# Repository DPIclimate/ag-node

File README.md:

<h2 align="center">
    Agriculture Node
</h2>
<p align="center">
  <a href="#about">About</a> •
  <a href="#schematic">Schematic</a> •
  <a href="#protocol / algorithm">Protocol</a> •
  <a href="#firmware docs">Docs</a> •
  <a href="#license">License</a>
</p>

<p align="center">
  
</p>

## About

The agriculture node (ag-node) is an automatic multi-weigh-station for measuring the live-weight of sheep  in remote locations. The station can be situated against a trough for which sheep weights will be recorded as they access feed or water. An in-built LoRaWAN radio sends data (containing live-weight information) back to a local gateway and onto the end user. Additional interfaces are provided, including; SDI-12, I<sub>2</sub>C and OneWire to allow for various sensors to be connected to the device (such as trough level sensors, temperature monitors etc.).

## Schematic

The devices schematic can be found at: [schematic.pdf](https://github.com/DPIclimate/ag-node/blob/master/figures/schematic.pdf)

Basic components are summarised in the below image. Where A is the analog-to-digital converter, B is the LoRaWAN communication infrastructure and C is the peripheral sensor connectors (I<sub>2</sub>C, OneWire and SDI-12).

<div align="middle"> 
	
</div>

## Protocol / Algorithm

As the device operates autonomously (sheep are weighed in an unsupervised manner) an algorithm to capture the maximum stable weight (and an error representation) is provided.

The protocol is explained below and a visual representation is provided.

1. A weight is captured (triggered by a sheep stepping on a scale) consisting of a time-series of weights while the sheep is on the platform

2. This time-series data is sliced into groups of 5 values

3. The slope between the first and last value is calculated (where values < 0.1) are discarded as they represent unstable weights

4. The Root Mean Square Error (RMSE) of the fitted line is calculated

5. The average of the 5 points are taken

6. An evaluation of the new weight is made against previous slices (see figure below under the Method `Evaluate` for an equation that represents this)

<div align="middle"> 
	
</div>

## Firmware Docs

Firmware documentation can be found [here](https://dpiclimate.github.io/ag-node)

An illustration of the devices operations can be found below:

<div align="middle"> 
	
</div>

## License

Ag-node is MIT licensed, as found in the [LICENSE](https://github.com/DPIclimate/ag-node/blob/master/LICENSE) file.

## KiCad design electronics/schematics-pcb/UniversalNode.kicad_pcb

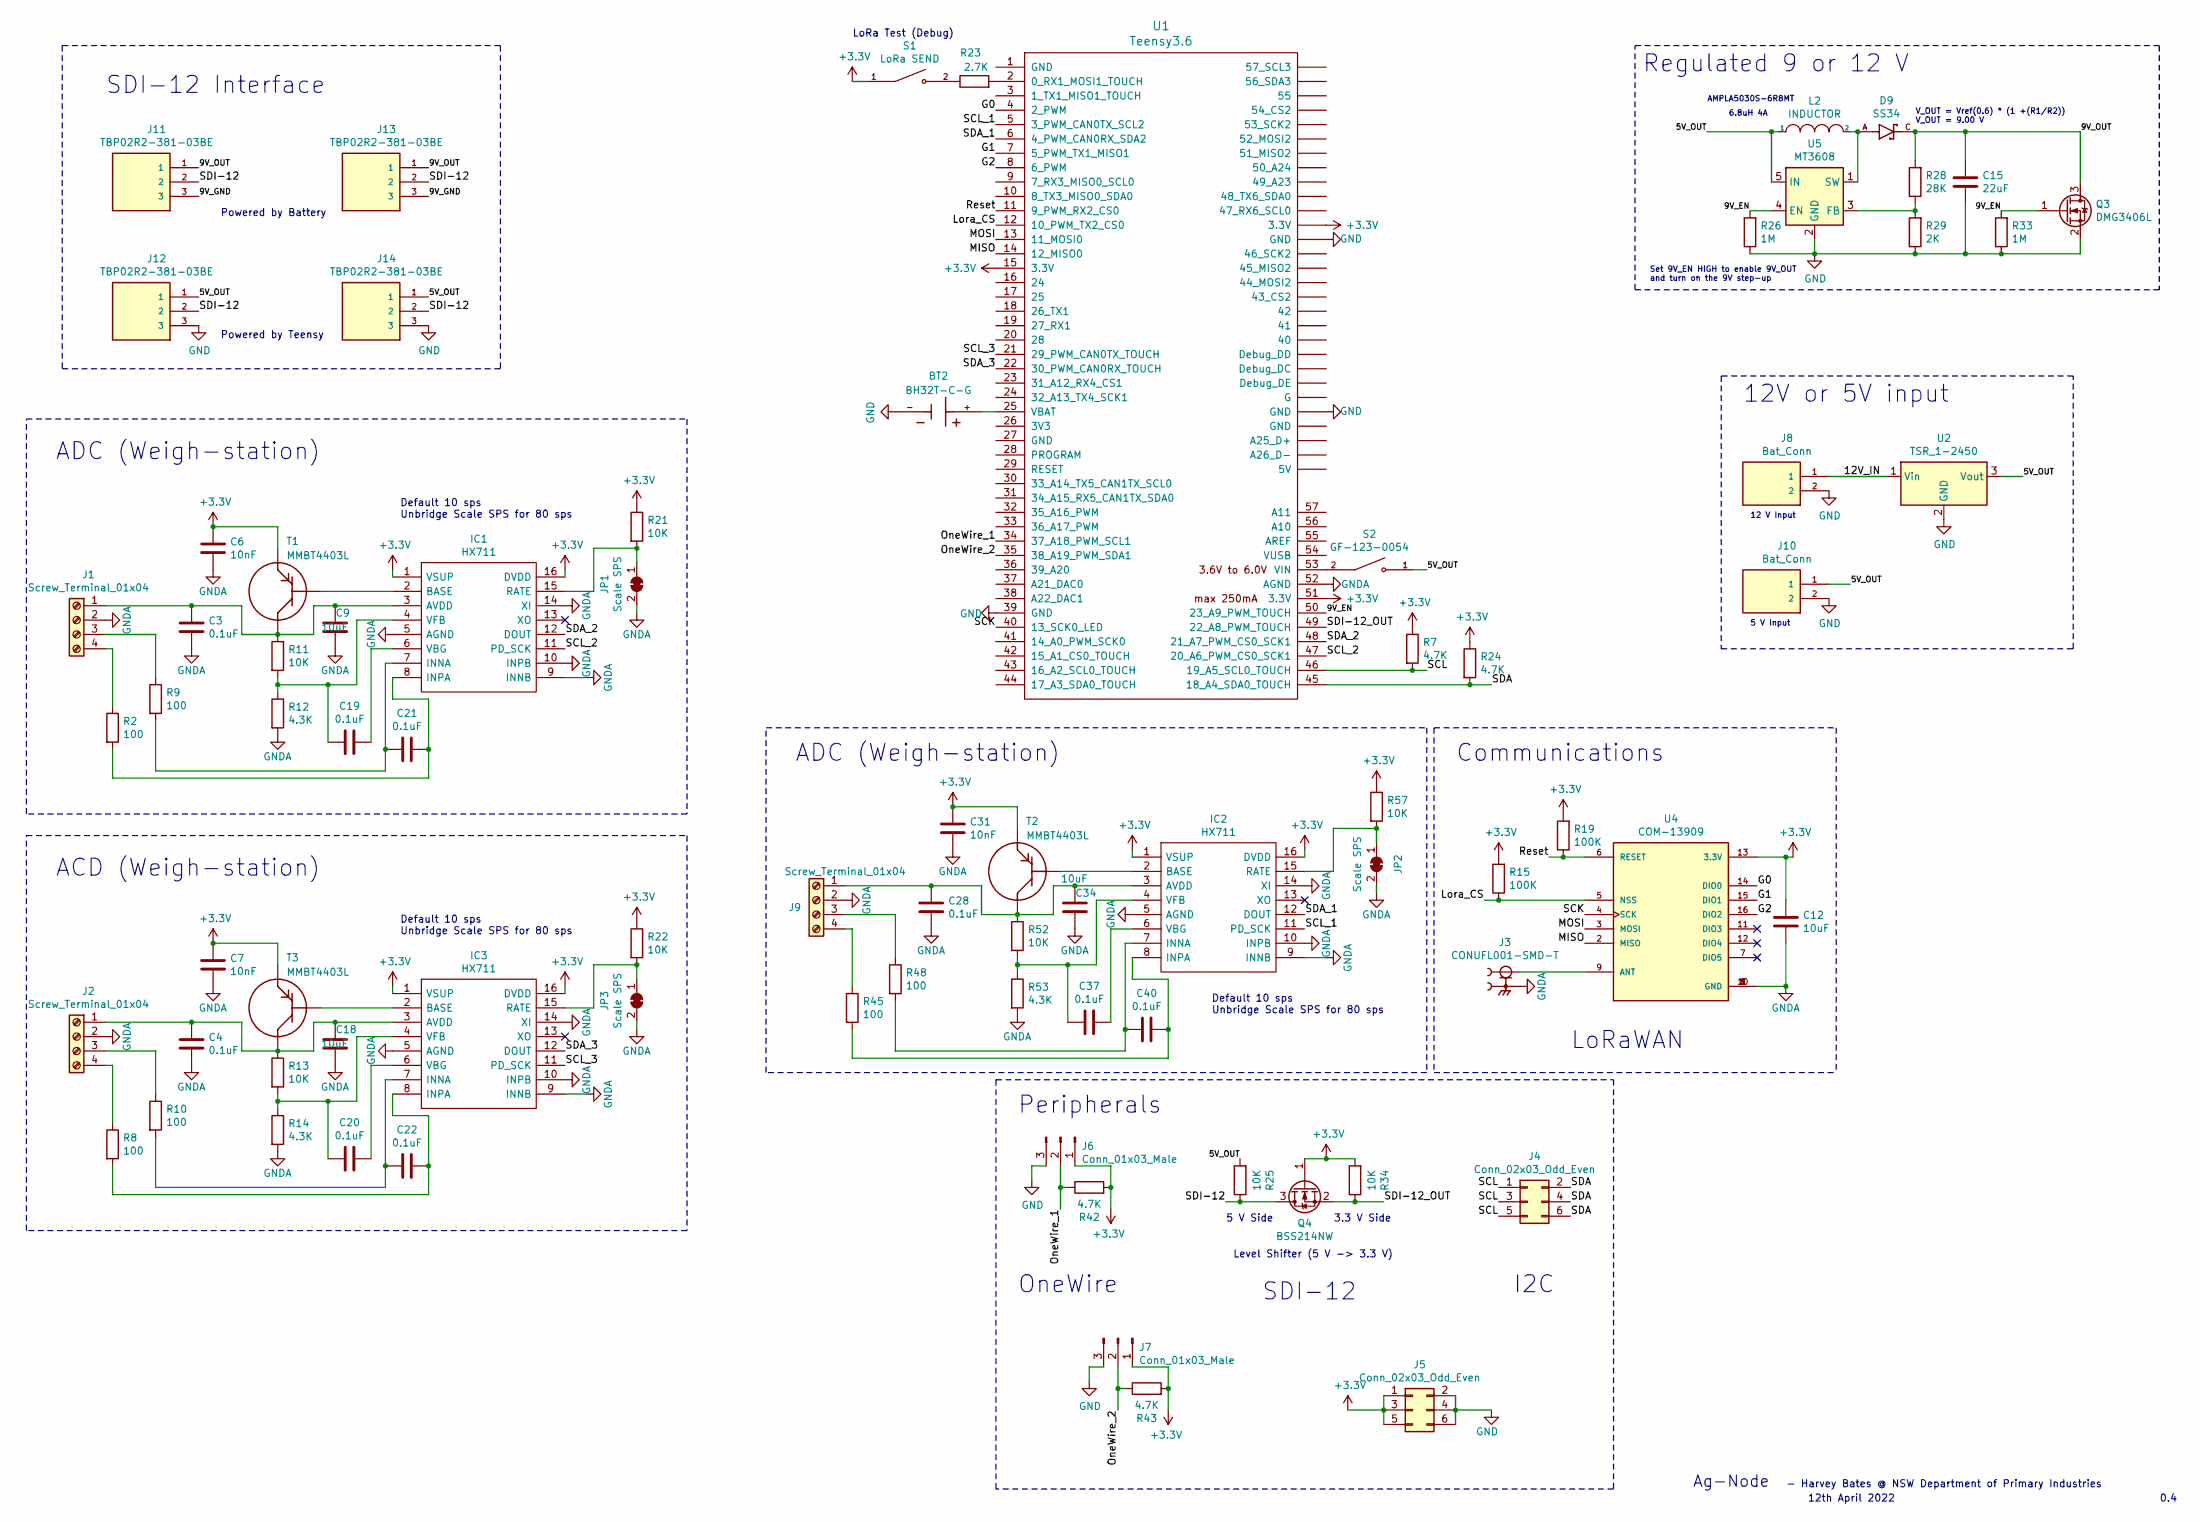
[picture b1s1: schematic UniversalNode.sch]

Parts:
BT2: BH32T-C-G; BAT_BH32T-C-G; PARTREV B
C3, C4, C19, C20, C21, C22, C28, C37, C40: 0.1uF; C_0805_2012Metric
C6, C7, C31: 10nF; C_0805_2012Metric
C9, C12, C18, C34: 10uF; CP_Elec_5x5.4
C15: 22uF; CP_Elec_6.3x5.9
D9: SS34; DIOM7959X265N; PARTREV 31 Aug 2016
IC1, IC2, IC3: HX711; SOIC127P600X160-16N; Manufacturer_Part_Number HX711
J1, J2, J9: Screw_Terminal_01x04; OSTOQ043250
J3: CONUFL001-SMD-T; LINX_CONUFL001-SMD-T; PARTREV B
J4, J5: Conn_02x03_Odd_Even; PinSocket_2x03_P2.54mm_Vertical
J6, J7: Conn_01x03_Male; PinSocket_1x03_P2.54mm_Vertical
J8, J10: Bat_Conn; 102-6492-ND‎
J11, J12, J13, J14: TBP02R2-381-03BE; CUI_TBP02R2-381-03BE
JP1, JP2, JP3: Scale SPS; SolderJumper-2_P1.3mm_Bridged_Pad1.0x1.5mm
L2: INDUCTOR; AMPLA5030S-6R8MT
Q3: DMG3406L; SOT-23
Q4: BSS214NW; SOT-323_SC-70
R2, R8, R9, R10, R45, R48: 100; R_0805_2012Metric
R7, R24, R42, R43: 4.7K; R_0805_2012Metric
R11, R13, R21, R22, R25, R34, R52, R57: 10K; R_0805_2012Metric
R12, R14, R53: 4.3K; R_0805_2012Metric
R15, R19: 100K; R_0805_2012Metric
R23: 2.7K; R_0805_2012Metric
R26, R33: 1M; R_0805_2012Metric
R28: 28K; R_0805_2012Metric
R29: 2K; R_0805_2012Metric
S1: LoRa SEND; SW_PTS636_SM43J_SMTR_LFS; PARTREV 27 mar 19
S2: GF-123-0054; SW_GF-123-0054; PARTREV May 20, 2003
T1, T2, T3: MMBT4403L; SOT23
U1: Teensy3.6; Teensy35_36
U2: TSR_1-2450; Converter_DCDC_TRACO_TSR-1_THT
U4: COM-13909; MOD_COM-13909
U5: MT3608; SOT-23-6

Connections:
+3V3: C6.1, C7.1, C12.1, C31.1, IC1.1 (VSUP), IC1.16 (DVDD), IC2.1 (VSUP), IC2.16 (DVDD), IC3.1 (VSUP), IC3.16 (DVDD), J5.1, J5.3, J5.5, J6.1, J7.1, Q4.1 (G), R7.1, R15.2, R19.2, R21.1, R22.1, R24.1, R34.2, R42.2, R43.2, R57.1, S1.1, T1.2, T2.2, T3.2, U1.15 (3.3V), U1.51 (3.3V), U1.~ (3.3V), U4.13 (3.3V)
/5V_OUT: J10.1, J12.1, J14.1, L2.1, R25.2, S2.1, U2.3 (Vout), U5.5 (IN)
/9V_EN: Q3.1 (G), R26.2, R33.2, U1.50 (23_A9_PWM_TOUCH), U5.4 (EN)
/9V_GND: J11.3, J13.3
/9V_OUT: C15.1, D9.C, J11.1, J13.1, Q3.3 (D), R28.2
/12V_IN: J8.1, U2.1 (Vin)
/G0: U1.4 (2_PWM), U4.14 (DIO0)
/G1: U1.7 (5_PWM_TX1_MISO1), U4.15 (DIO1)
/G2: U1.8 (6_PWM), U4.16 (DIO2)
/Lora_CS: R15.1, U1.12 (10_PWM_TX2_CS0), U4.5 (NSS)
/MISO: U1.14 (12_MISO0), U4.2 (MISO)
/MOSI: U1.13 (11_MOSI0), U4.3 (MOSI)
/OneWire_1: J6.2, R42.1, U1.34 (37_A18_PWM_SCL1)
/OneWire_2: J7.2, R43.1, U1.35 (38_A19_PWM_SDA1)
/Reset: R19.1, U1.11 (9_PWM_RX2_CS0), U4.6 (RESET)
/SCK: U1.40 (13_SCK0_LED), U4.4 (SCK)
/SCL: J4.1, J4.3, J4.5, R7.2, U1.46 (19_A5_SCL0_TOUCH)
/SCL_1: IC2.11 (PD_SCK), U1.5 (3_PWM_CAN0TX_SCL2)
/SCL_2: IC1.11 (PD_SCK), U1.47 (20_A6_PWM_CS0_SCK1)
/SCL_3: IC3.11 (PD_SCK), U1.21 (29_PWM_CAN0TX_TOUCH)
/SDA: J4.2, J4.4, J4.6, R24.2, U1.45 (18_A4_SDA0_TOUCH)
/SDA_1: IC2.12 (DOUT), U1.6 (4_PWM_CAN0RX_SDA2)
/SDA_2: IC1.12 (DOUT), U1.48 (21_A7_PWM_CS0_SCK1)
/SDA_3: IC3.12 (DOUT), U1.22 (30_PWM_CAN0RX_TOUCH)
/SDI-12: J11.2, J12.2, J13.2, J14.2, Q4.3 (D), R25.1
/SDI-12_OUT: Q4.2 (S), R34.1, U1.49 (22_A8_PWM_TOUCH)
GND: BT2.-, C15.2, J5.2, J5.4, J5.6, J6.3, J7.3, J8.2, J10.2, J12.3, J14.3, Q3.2 (S), R26.1, R29.1, R33.1, U1.39 (GND), U1.~ (3.3V), U2.2 (GND), U5.2 (GND)
GNDA: C3.2, C4.2, C6.2, C7.2, C9.2, C12.2, C18.2, C28.2, C31.2, C34.2, IC1.5 (AGND), IC1.9 (INNB), IC1.10 (INPB), IC1.14 (XI), IC2.5 (AGND), IC2.9 (INNB), IC2.10 (INPB), IC2.14 (XI), IC3.5 (AGND), IC3.9 (INNB), IC3.10 (INPB), IC3.14 (XI), J1.2, J2.2, J3.2, J3.3, J9.2, JP1.2 (B), JP2.2 (B), JP3.2 (B), R12.2, R14.2, R53.2, U1.52 (AGND), U4.1 (GND), U4.8 (GND), U4.10 (GND)
unnamed: BT2.+, U1.25 (VBAT)
unnamed: C3.1, C9.1, IC1.3 (AVDD), J1.1, R11.1, T1.3
unnamed: C4.1, C18.1, IC3.3 (AVDD), J2.1, R13.1, T3.3
unnamed: C19.1, IC1.6 (VBG)
unnamed: C19.2, IC1.4 (VFB), R11.2, R12.1
unnamed: C20.1, IC3.6 (VBG)
unnamed: C20.2, IC3.4 (VFB), R13.2, R14.1
unnamed: C21.1, IC1.7 (INNA), R9.2
unnamed: C21.2, IC1.8 (INPA), R2.2
unnamed: C22.1, IC3.7 (INNA), R10.2
unnamed: C22.2, IC3.8 (INPA), R8.2
unnamed: C28.1, C34.1, IC2.3 (AVDD), J9.1, R52.1, T2.3
unnamed: C37.1, IC2.6 (VBG)
unnamed: C37.2, IC2.4 (VFB), R52.2, R53.1
unnamed: C40.1, IC2.7 (INNA), R48.2
unnamed: C40.2, IC2.8 (INPA), R45.2
unnamed: D9.A, L2.2, U5.1 (SW)
unnamed: IC1.2 (BASE), T1.1
unnamed: IC1.15 (RATE), JP1.1 (A), R21.2
unnamed: IC2.2 (BASE), T2.1
unnamed: IC2.15 (RATE), JP2.1 (A), R57.2
unnamed: IC3.2 (BASE), T3.1
unnamed: IC3.15 (RATE), JP3.1 (A), R22.2
unnamed: J1.3, R9.1
unnamed: J1.4, R2.1
unnamed: J2.3, R10.1
unnamed: J2.4, R8.1
unnamed: J3.1, U4.9 (ANT)
unnamed: J9.3, R48.1
unnamed: J9.4, R45.1
unnamed: R23.1, S1.2
unnamed: R23.2, U1.2 (0_RX1_MOSI1_TOUCH)
unnamed: R28.1, R29.2, U5.3 (FB)
unnamed: S2.2, U1.53 (VIN)

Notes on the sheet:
Ag-Node
12th April 2022
- Harvey Bates @ NSW Department of Primary Industries
0.4
Powered by Battery
Powered by Teensy
SDI-12 Interface
ACD (Weigh-station)
Default 10 sps Unbridge Scale SPS for 80 sps
ADC (Weigh-station)
5 V Input
12V or 5V input
12 V Input
Set 9V_EN HIGH to enable 9V_OUT and turn on the 9V step-up
Regulated 9 or 12 V
V_OUT = Vref(0.6) * (1 +(R1/R2)) V_OUT = 9.00 V
AMPLA5030S-6R8MT
6.8uH 4A
LoRa Test (Debug)
OneWire
I2C
SDI-12
Level Shifter (5 V -> 3.3 V)
5 V Side
3.3 V Side
Peripherals
LoRaWAN
Communications

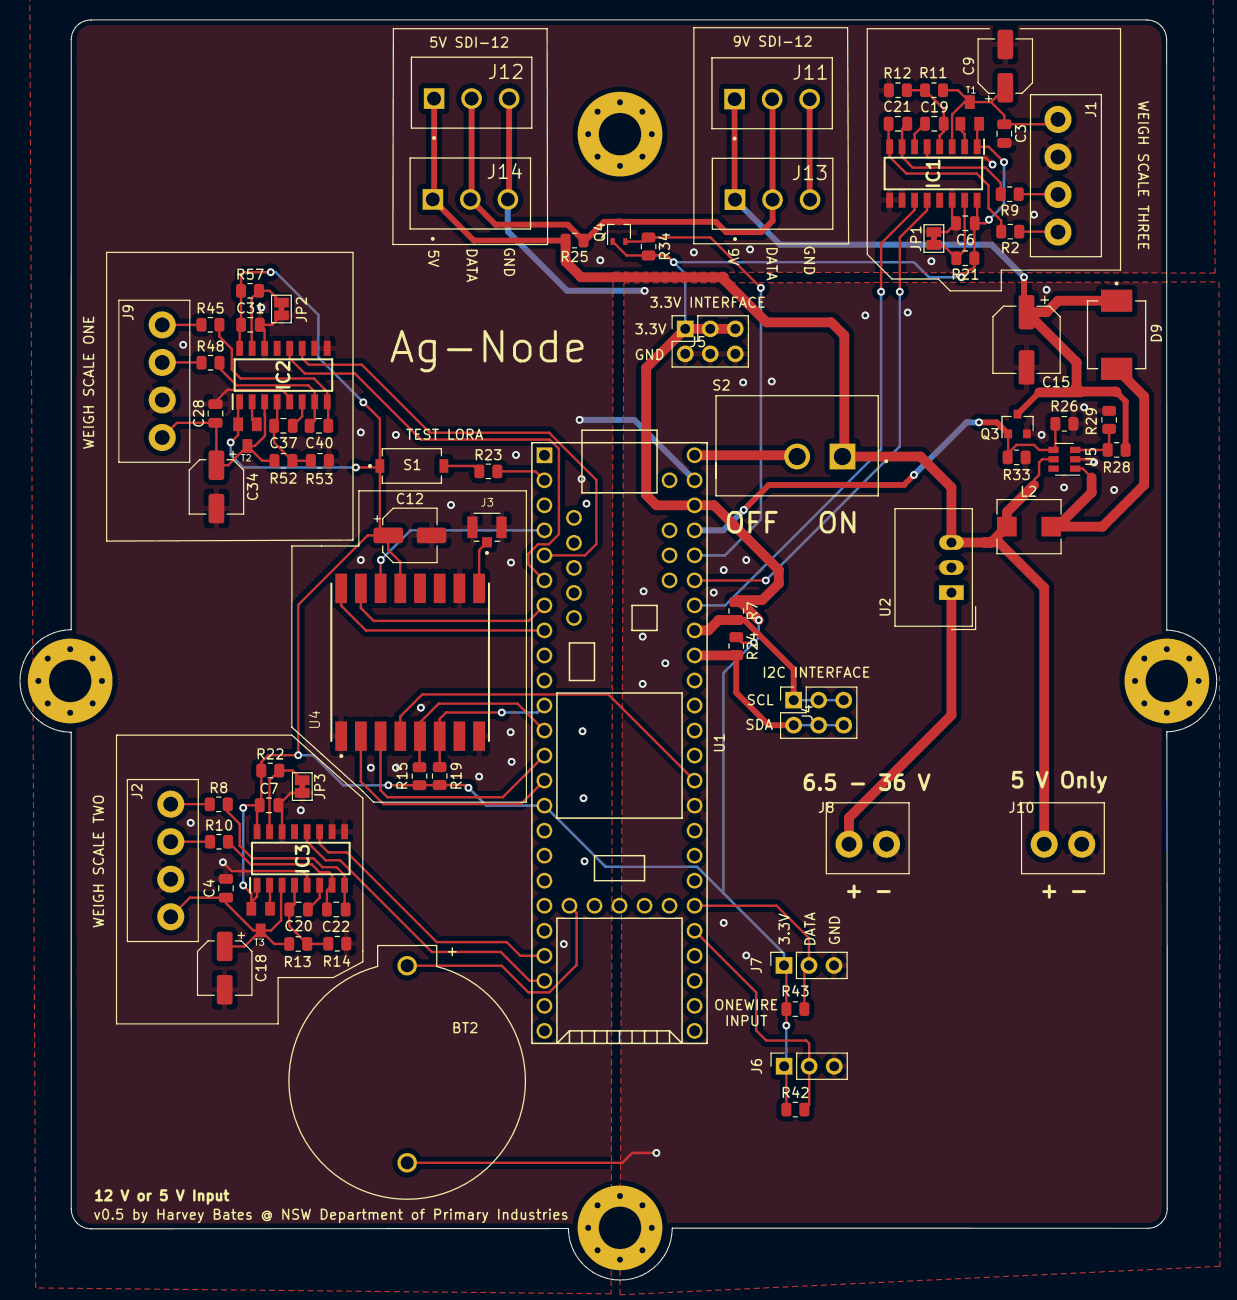
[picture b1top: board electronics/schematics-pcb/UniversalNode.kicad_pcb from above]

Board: 2 copper layers, 121.5 x 127.9 mm, 79 parts (0 on the bottom side), 62 nets.

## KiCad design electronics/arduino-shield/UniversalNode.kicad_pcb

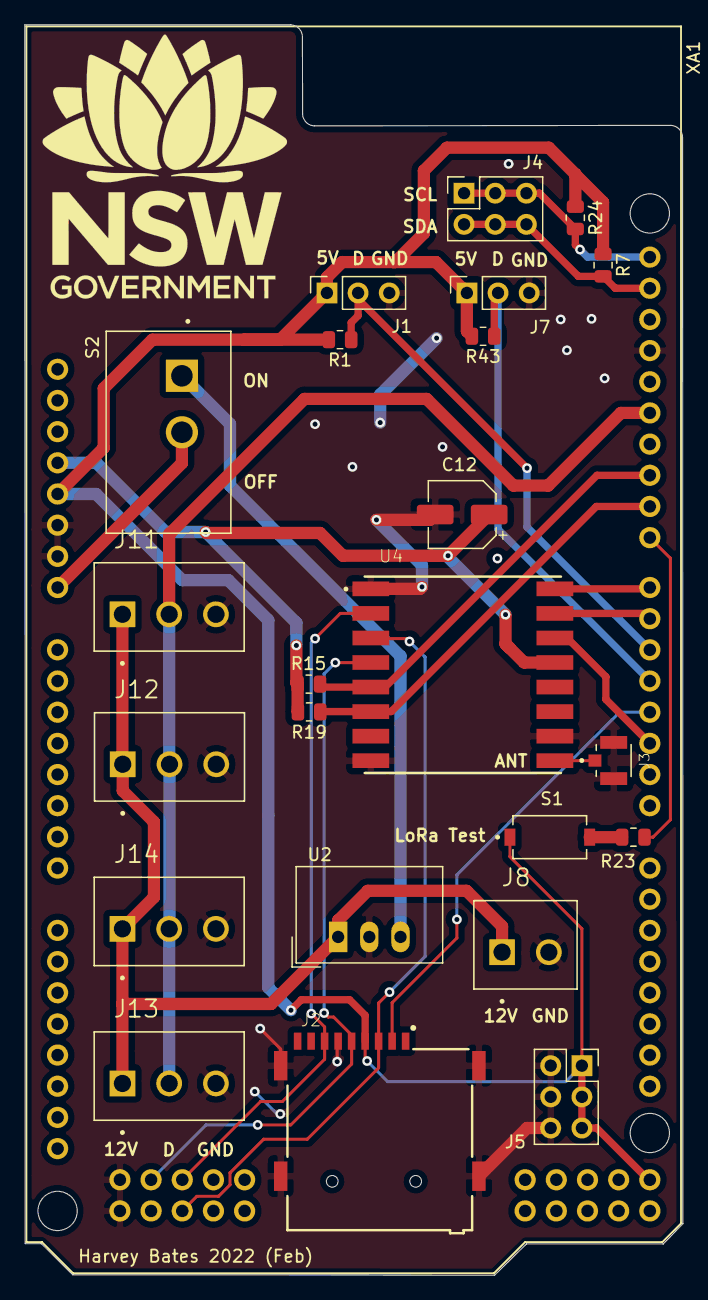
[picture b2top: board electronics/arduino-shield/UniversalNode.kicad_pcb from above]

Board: 2 copper layers, 53.6 x 101.9 mm, 24 parts (0 on the bottom side), 23 nets.

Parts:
C12: 10uF; CP_Elec_5x5.4
J1, J7: Conn_01x03_Male; PinSocket_1x03_P2.54mm_Vertical
J2: MEM2075-00-140-01-A; GCT_MEM2075-00-140-01-A
J3: CONUFL001-SMD-T; LINX_CONUFL001-SMD-T
J4, J5: Conn_02x03_Odd_Even; PinSocket_2x03_P2.54mm_Vertical
J8: Bat_Conn; CUI_TBP02R2-381-02BE
J11, J12, J13, J14: TBP02R2-381-03BE; CUI_TBP02R2-381-03BE
R1, R7, R24, R43: 4.7K; R_0805_2012Metric
R15, R19: 100K; R_0805_2012Metric
R23: 2.7K; R_0805_2012Metric
S1: LoRa SEND; SW_PTS636_SM43J_SMTR_LFS
S2: GF-123-0054; SW_GF-123-0054
U2: TSR_1-2450; Converter_DCDC_TRACO_TSR-1_THT
U4: COM-13909; MOD_COM-13909
XA1: Arduino_Mega2560_Shield

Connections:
+3V3: C12.1, R15.2, R19.2, U4.13, XA1.3V3
/5V: J1.1, J2.P4, J5.1, J5.3, J5.5, J7.1, R1.2, R7.1, R24.1, R43.2, S1.1, XA1.5V1, XA1.5V3
/5V_OUT: S2.1, U2.3
/12V_IN: J8.1, J11.1, J12.1, J13.1, J14.1, U2.1
/G0: U4.14, XA1.D2
/G1: U4.15, XA1.D6
/G2: U4.16, XA1.D7
/Lora_CS: R15.1, U4.5, XA1.D10
/MISO: J2.P7, U4.2, XA1.D50
/MOSI: J2.P3, U4.3, XA1.D51
/OneWire_1: J7.2, R43.1, XA1.D4
/OneWire_2: J1.2, R1.1, XA1.D5
/Reset: R19.1, U4.6, XA1.D9
/SCK: J2.P5, U4.4, XA1.D52
/SCL: J4.1, J4.3, J4.5, R24.2, XA1.SCL
/SDA: J4.2, J4.4, J4.6, R7.2, XA1.SDA
/SDI-12: J11.2, J12.2, J13.2, J14.2, XA1.D12
/SD_CS: J2.P2, XA1.D3
GND: C12.2, J1.3, J2.P6, J2.SH1, J2.SH2, J2.SH3, J2.SH4, J3.2, J3.3, J5.2, J5.4, J5.6, J7.3, J8.2, J11.3, J12.3, J13.3, J14.3, U2.2, U4.1, U4.8, U4.10, XA1.GND1, XA1.GND2, XA1.GND3, XA1.GND5, XA1.GND6
unnamed: J3.1, U4.9
unnamed: R23.1, S1.2
unnamed: R23.2, XA1.D8
unnamed: S2.2, XA1.VIN

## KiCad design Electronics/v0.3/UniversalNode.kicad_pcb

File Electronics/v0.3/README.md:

## Version 0.3
- Uses Teensy 3.6 as mainboard controller (run at a low clock speed) and defaults to sleep
- Has 3 weigh station ports (controlled by a HX711 and a ATMega328) 
- ATMega328's have interrupts connected to the teensy to wake it up when they want to transfer some data (over I2C)
- Single lorawan module (connected to teensy, can sleep when not in use)
- Designed to be a low-power device with multiple processors for asynchronous readings

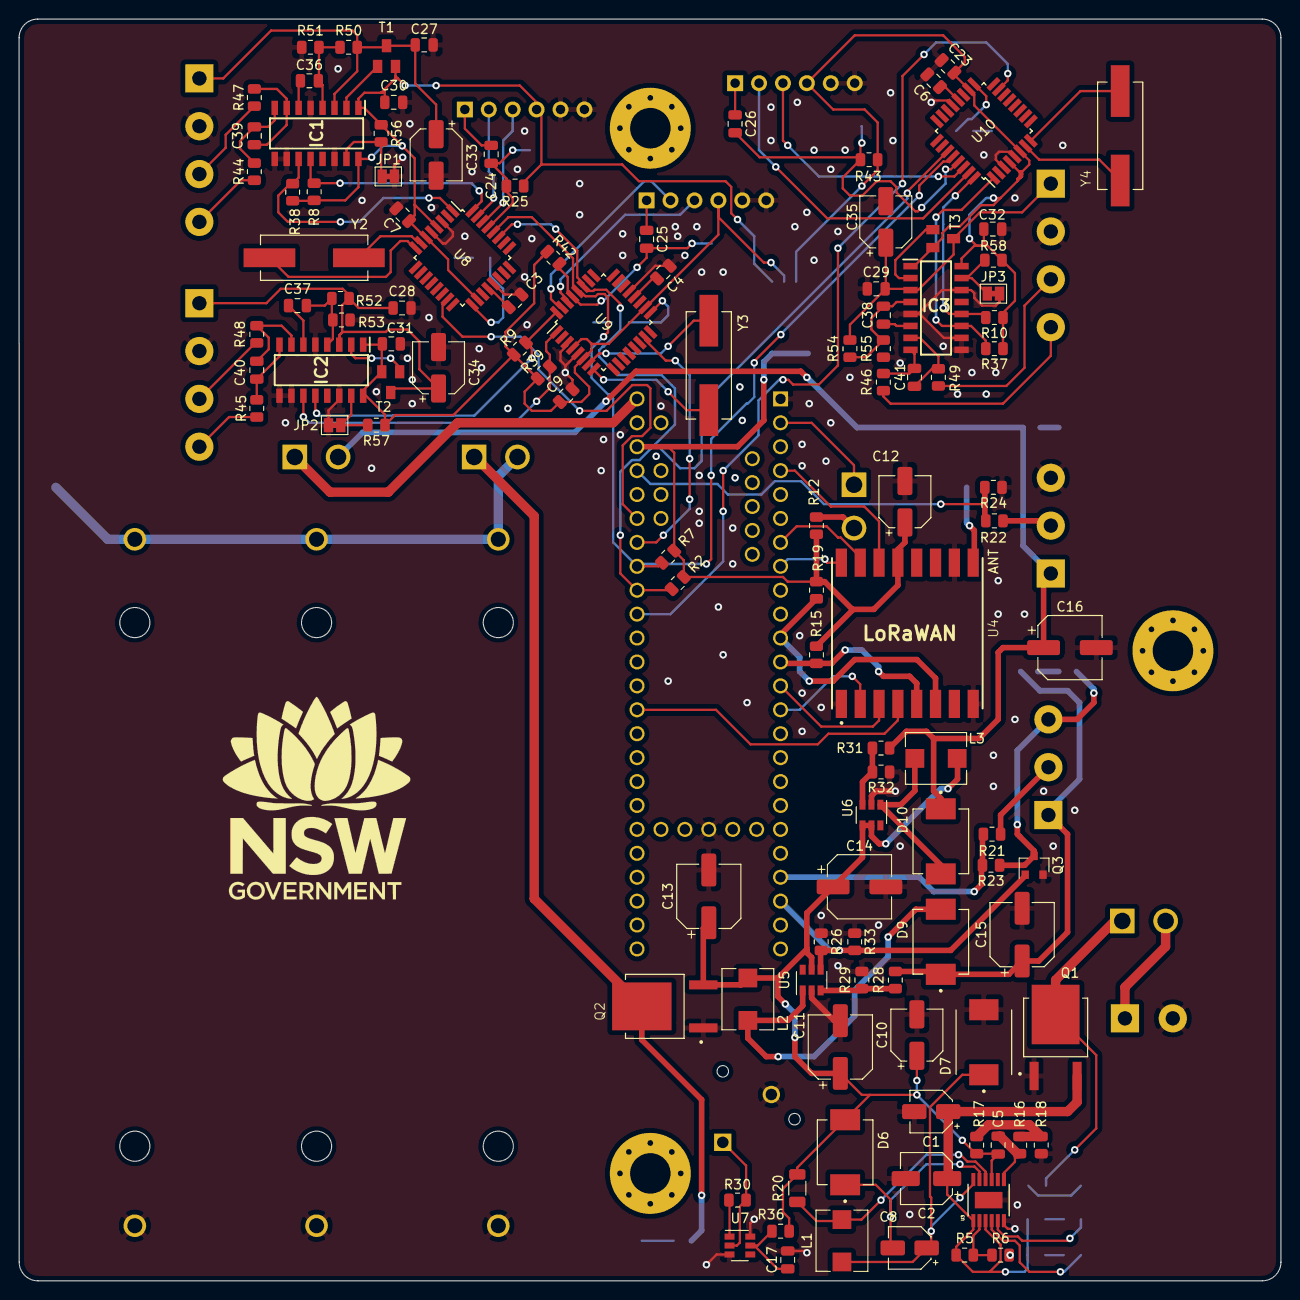
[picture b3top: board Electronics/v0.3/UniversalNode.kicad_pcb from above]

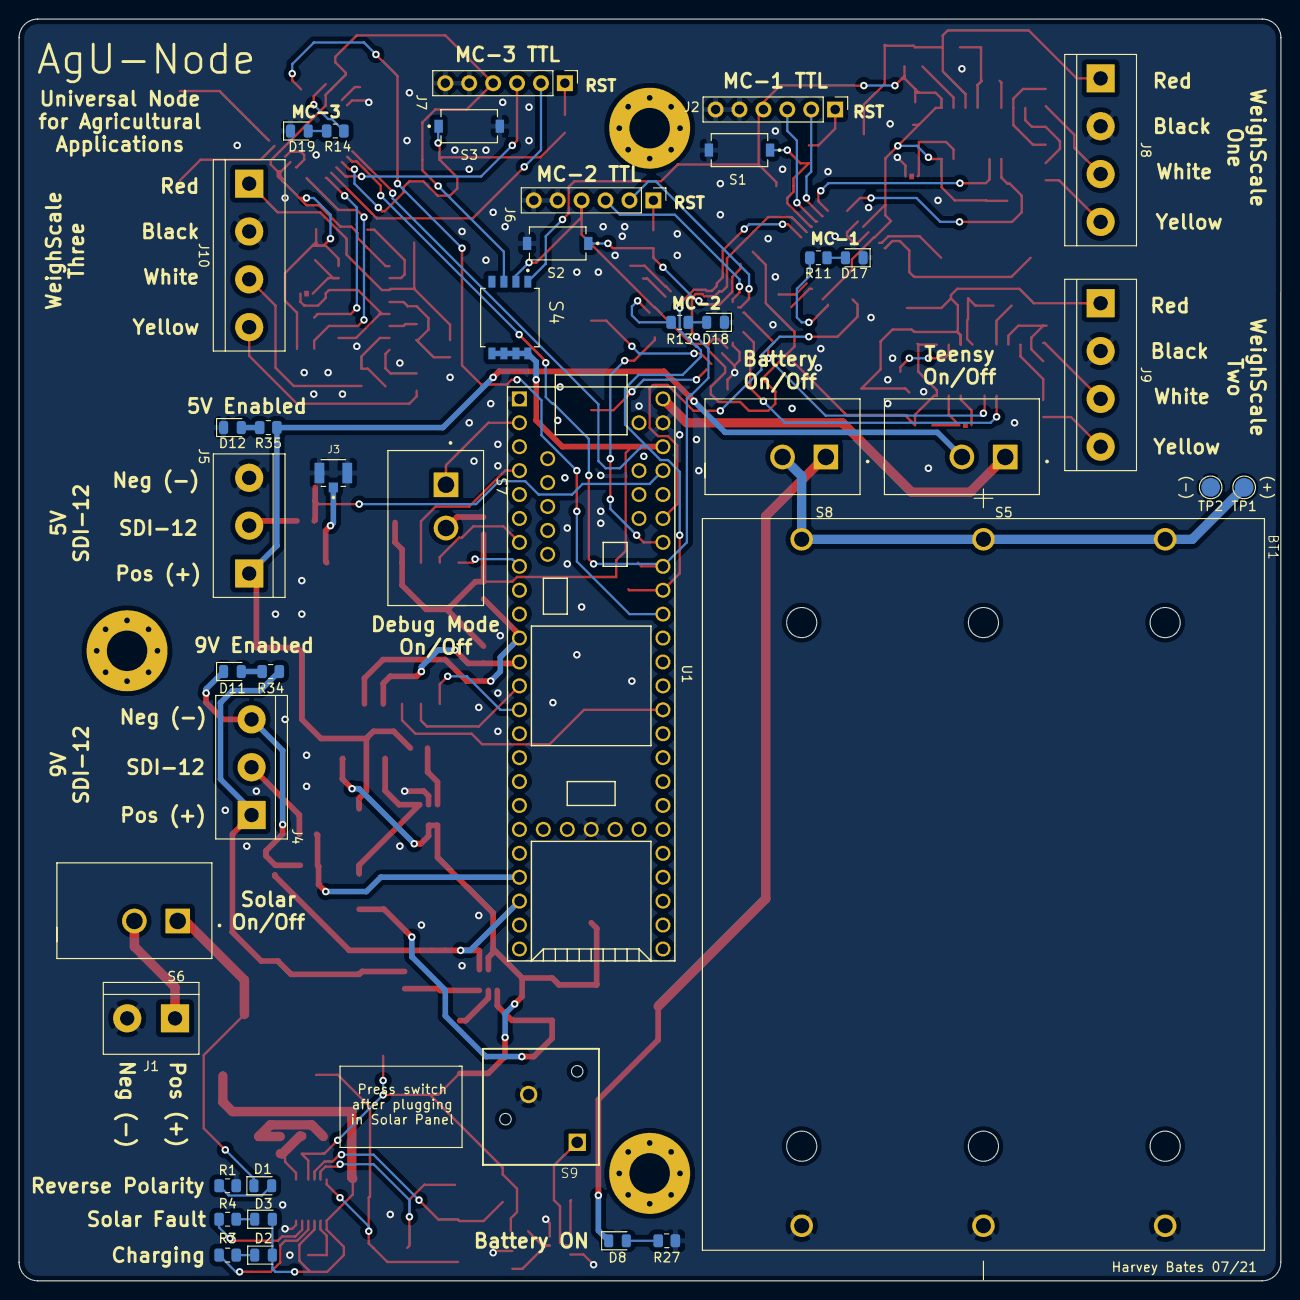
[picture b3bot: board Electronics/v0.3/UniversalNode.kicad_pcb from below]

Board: 2 copper layers, 134.0 x 134.0 mm, 154 parts (41 on the bottom side), 117 nets.

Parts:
BT1: BK-18650-PC6; BAT_BK-18650-PC6
C1, C8: 1uF; CP_Elec_4x5.4
C2, C10, C12, C33, C34, C35: 10uF; CP_Elec_5x5.4
C3, C4, C6, C7, C9, C17, C23, C24, C25, C26, C27, C28, C29, C36, C37, C38, C39, C40, C41: 0.1uF; C_0805_2012Metric
C5: 30pF; C_0805_2012Metric
C11: 100uF; CP_Elec_6.3x5.9
C13, C14, C15, C16: 22uF; CP_Elec_6.3x5.9
C30, C31, C32: 10nF; C_0805_2012Metric
D1, D2, D3, D8, D11, D12, D17, D18, D19: LED; LED_0805_2012Metric
D6, D9, D10: SS34; DIOM7959X265N
D7: MBRS340; DIOM7959X261N
IC1, IC2, IC3: HX711; SOIC127P600X160-16N
J1: Screw_Terminal_01x02; TerminalBlock_bornier-2_P5.08mm
J2, J6, J7: Conn_01x06_Male; PinHeader_1x06_P2.54mm_Vertical
J3: CONUFL001-SMD-T; LINX_CONUFL001-SMD-T
J4, J5: Screw_Terminal_01x03; TerminalBlock_bornier-3_P5.08mm
J8, J9, J10: Screw_Terminal_01x04; TerminalBlock_bornier-4_P5.08mm
JP1, JP2, JP3: Scale SPS; SolderJumper-2_P1.3mm_Bridged_Pad1.0x1.5mm
L1, L2, L3: INDUCTOR; AMPLA5030S-6R8MT
Q1, Q2: AOD417; DPAK228P994X240_3N
Q3: DMG3406L; SOT-23
R1: 4.7K; R_0805_2012Metric
R2, R3, R4, R7, R8, R9, R10, R12, R25, R35, R37, R38, R39, R42, R43, R56, R57, R58: 10K; R_0805_2012Metric
R5: 220K; R_0805_2012Metric
R6, R15, R19: 100K; R_0805_2012Metric
R11, R13, R14: 330; R_0805_2012Metric
R16: 180K; R_0805_2012Metric
R17: 91K; R_0805_2012Metric
R18: 330K; R_0805_2012Metric
R20: 0.05(RS); R_1206_3216Metric
R21, R28: 28K; R_0805_2012Metric
R22, R31, R50, R52, R54: 20K; R_0805_2012Metric
R23: 16K; R_0805_2012Metric
R24: 40K; R_0805_2012Metric
R26, R33: 1M; R_0805_2012Metric
R27, R29: 2K; R_0805_2012Metric
R30: 1K; R_0805_2012Metric
R32: 2.7K; R_0805_2012Metric
R34: 15K; R_0805_2012Metric
R36, R44, R45, R46, R47, R48, R49: 100; R_0805_2012Metric
R51, R53, R55: 8.2K; R_0805_2012Metric
S1, S2, S3: PTS636_SM43J_SMTR_LFS; SW_PTS636_SM43J_SMTR_LFS
S4: TDA04H0SB1; SW_TDA04H0SB1
S5, S6, S7, S8: GF-123-0054; SW_GF-123-0054
S9: KS11R21CQD; SW_KS11R21CQD
T1, T2, T3: MMBT4403L; SOT23
TP1: Bat+; TestPoint_Pad_D2.0mm
TP2: Bat-; TestPoint_Pad_D2.0mm
U1: Teensy3.6; Teensy35_36
U3: LT3652IMSETRPBF; MSOP-12_MSE
U4: COM-13909; MOD_COM-13909
U5, U6: MT3608; SOT-23-6
U7: DW06D; SOT-23-6
U8, U9, U10: ATmega328-AU; TQFP-32_7x7mm_P0.8mm
Y2, Y3, Y4: 9C-8.000MEEJ-T; XTAL_9C-8.000MEEJ-T

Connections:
+3V3: C12.1, R2.1, R7.1, R12.1, R15.2, R19.2, S4.5, S4.6, S4.7, S4.8, U1.51, U4.13
/1_DTR: C24.1, J2.1
/1_Reset: C24.2, R25.2, S1.1, U8.29
/1_Rx: J2.3, U8.30
/1_SCK: R11.2, U8.17
/1_SCL: IC1.11, R38.2, U8.1
/1_SDA: IC1.12, R8.2, U8.32
/1_Tx: J2.2, U8.31
/2_DTR: C25.1, J6.1
/2_Reset: C25.2, R42.2, S2.1, U9.29
/2_Rx: J6.3, U9.30
/2_SCK: R13.2, U9.17
/2_SCL: IC2.11, R39.2, U9.1
/2_SDA: IC2.12, R9.2, U9.32
/2_Tx: J6.2, U9.31
/3.3_1: C7.1, C30.1, IC1.1, IC1.16, J2.4, R8.1, R25.1, R38.1, R56.1, S4.1, T1.2, U8.4, U8.6, U8.18
/3.3_2: C9.1, C31.1, IC2.1, IC2.16, J6.4, R9.1, R39.1, R42.1, R57.1, S4.2, T2.2, U9.4, U9.6, U9.18
/3.3_3: C23.1, C32.1, IC3.1, IC3.16, J7.4, R10.1, R37.1, R43.1, R58.1, S4.3, T3.2, U10.4, U10.6, U10.18
/3_DTR: C26.1, J7.1
/3_Reset: C26.2, R43.2, S3.1, U10.29
/3_Rx: J7.3, U10.30
/3_SCK: R14.2, U10.17
/3_SCL: IC3.11, R37.2, U10.1
/3_SDA: IC3.12, R10.2, U10.32
/3_Tx: J7.2, U10.31
/5V-SDI-12: R22.1, R24.2, U1.50
/5V_OUT: C16.1, D10.C, J5.1, R31.2, R35.2, S5.2
/9V-SDI-12: R21.1, R23.2, U1.21
/9V_EN: Q3.1, R26.2, R33.2, U1.22, U5.4
/9V_GND: D11.1, J4.3, Q3.3, R23.1
/9V_OUT: C15.1, D9.C, J4.1, R28.2, R34.2
/Debug(INT): S7.1, U1.2
/G0: U1.4, U4.14
/G1: U1.7, U4.15
/G2: U1.8, U4.16
/INT_Teensy1: U1.48, U8.15
/INT_Teensy2: U1.47, U9.15
/INT_Teensy3: U1.44, U10.15
/Lora_CS: R15.1, U1.12, U4.5
/MISO: U1.14, U4.2
/MOSI: U1.13, U4.3
/Reset: R19.1, U1.11, U4.6
/SCK: U1.40, U4.4
/SCL: R7.2, U1.46, U8.28, U9.28, U10.28
/SDA: R2.2, U1.45, U8.27, U9.27, U10.27
/SOLAR_IN: C1.1, C2.1, D2.2, D3.2, Q1.3, R5.1, U3.1, U3.3
/VIN_REG: R5.2, R6.1, U3.2
/V_BAT: C5.1, C10.1, C11.1, C13.1, C14.1, D6.A, L2.1, L3.1, Q2.3, R17.2, R20.1, R36.1, U3.9, U5.5, U6.4, U6.5
GND: BT1.1, BT1.2, BT1.3, C1.2, C2.2, C3.2, C4.2, C6.2, C7.2, C9.2, C10.2, C11.2, C12.2, C13.2, C14.2, C15.2, C16.2, C17.2, C23.2, C27.2, C28.2, C29.2, C30.2, C31.2, C32.2, C33.2, C34.2, C35.2, D7.A, D12.1, D17.1, D18.1, D19.1, IC1.5, IC1.9, IC1.10, IC1.14, IC2.5, IC2.9, IC2.10, IC2.14, IC3.5, IC3.9, IC3.10, IC3.14, J1.2, J2.5, J2.6, J3.2, J3.3, J5.3, J6.5, J6.6, J7.5, J7.6, J8.2, J9.2, J10.2, JP1.2, JP2.2, JP3.2, Q1.1, Q2.1, Q3.2, R1.2, R6.2, R18.1, R24.1, R26.1, R27.2, R29.1, R32.1, R33.1, R51.2, R53.2, R55.2, S1.2, S2.2, S3.2, S9.3, TP2.1, U1.1, U1.27, U1.52, U3.6, U3.13, U4.1, U4.8, U4.10, U5.2, U6.2, U7.3, U7.6, U8.3, U8.5, U8.21, U9.3, U9.5, U9.21, U10.3, U10.5, U10.21
unnamed: BT1.1+, BT1.2+, BT1.3+, S8.2, TP1.1
unnamed: C3.1, U8.20
unnamed: C4.1, U9.20
unnamed: C5.2, R16.2, U3.7
unnamed: C6.1, U10.20
unnamed: C8.1, D7.C, L1.1, U3.12
unnamed: C8.2, D6.C, U3.11
unnamed: C17.1, R36.2, U7.5
unnamed: C27.1, C33.1, IC1.3, J8.1, R50.1, T1.3
unnamed: C28.1, C34.1, IC2.3, J9.1, R52.1, T2.3
unnamed: C29.1, C35.1, IC3.3, J10.1, R54.1, T3.3
unnamed: C36.1, IC1.6
unnamed: C36.2, IC1.4, R50.2, R51.1
unnamed: C37.1, IC2.6
unnamed: C37.2, IC2.4, R52.2, R53.1
unnamed: C38.1, IC3.6
unnamed: C38.2, IC3.4, R54.2, R55.1
unnamed: C39.1, IC1.7, R47.2
unnamed: C39.2, IC1.8, R44.2
unnamed: C40.1, IC2.7, R48.2
unnamed: C40.2, IC2.8, R45.2
unnamed: C41.1, IC3.7, R49.2
unnamed: C41.2, IC3.8, R46.2
unnamed: D1.1, Q1.4, S6.1
unnamed: D1.2, R1.1
unnamed: D2.1, R3.2
unnamed: D3.1, R4.2
unnamed: D8.1, Q2.4, S8.1
unnamed: D8.2, R27.1
unnamed: D9.A, L2.2, U5.1
unnamed: D10.A, L3.2, U6.1
unnamed: D11.2, R34.1
unnamed: D12.2, R35.1
unnamed: D17.2, R11.1
unnamed: D18.2, R13.1
unnamed: D19.2, R14.1
unnamed: IC1.2, T1.1
unnamed: IC1.15, JP1.1, R56.2
unnamed: IC2.2, T2.1
unnamed: IC2.15, JP2.1, R57.2
unnamed: IC3.2, T3.1
unnamed: IC3.15, JP3.1, R58.2
unnamed: J1.1, S6.2
unnamed: J3.1, U4.9
unnamed: J4.2, R21.2
unnamed: J5.2, R22.2
unnamed: J8.3, R47.1
unnamed: J8.4, R44.1
unnamed: J9.3, R48.1
unnamed: J9.4, R45.1
unnamed: J10.3, R49.1
unnamed: J10.4, R46.1
unnamed: L1.2, R20.2, U3.10
unnamed: R3.1, U3.4
unnamed: R4.1, U3.5
unnamed: R12.2, S7.2
unnamed: R16.1, R17.1, R18.2
unnamed: R28.1, R29.2, U5.3
unnamed: R30.1, U7.1
unnamed: R30.2, S9.1, U7.2
unnamed: R31.1, R32.2, U6.3
unnamed: S5.1, U1.53
unnamed: U8.7, Y2.1
unnamed: U8.8, Y2.2
unnamed: U9.7, Y3.1
unnamed: U9.8, Y3.2
unnamed: U10.7, Y4.1
unnamed: U10.8, Y4.2

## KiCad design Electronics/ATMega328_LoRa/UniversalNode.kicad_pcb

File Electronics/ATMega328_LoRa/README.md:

## Version 0.2
- Uses ATMega328 as mainboard controller
- Single lorawan module
- Has SD card reader on bottom
- J-Tag connector on the top

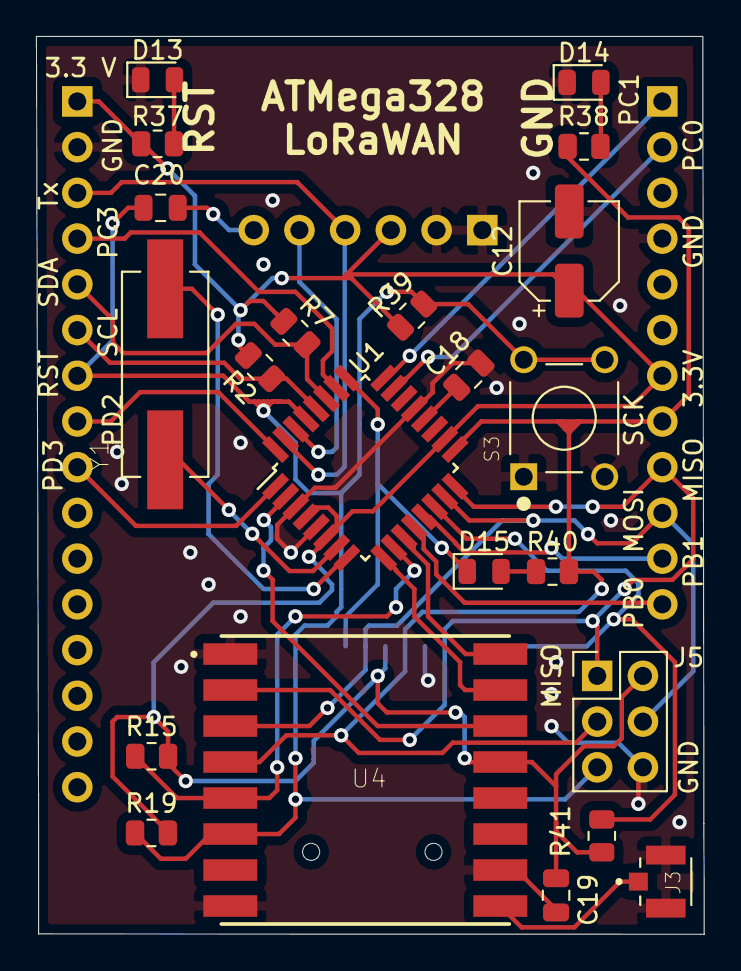
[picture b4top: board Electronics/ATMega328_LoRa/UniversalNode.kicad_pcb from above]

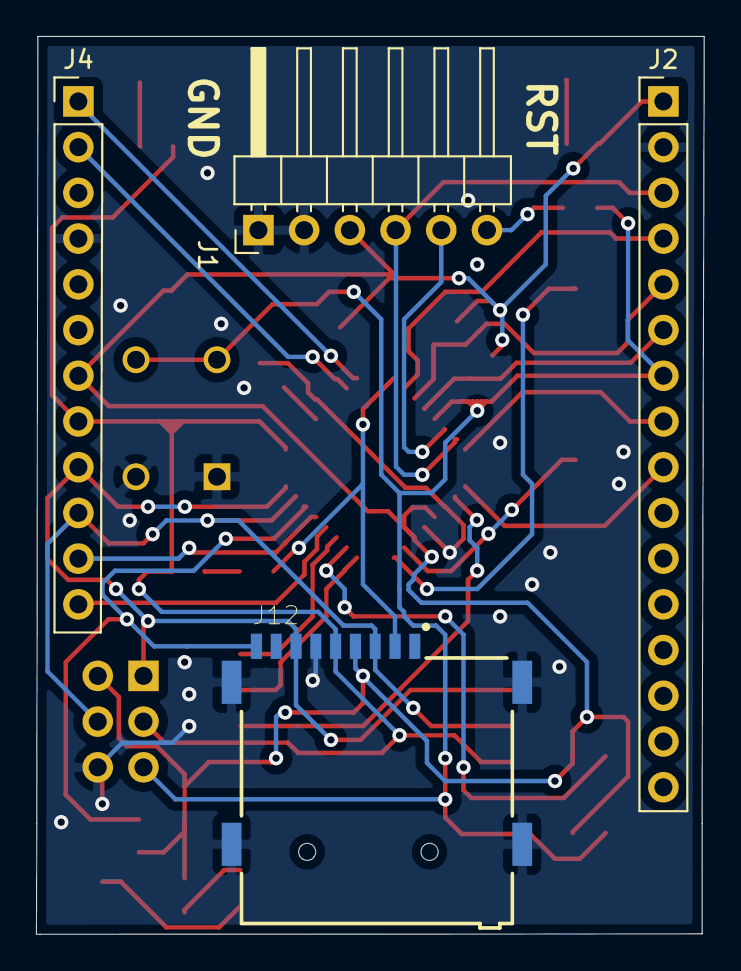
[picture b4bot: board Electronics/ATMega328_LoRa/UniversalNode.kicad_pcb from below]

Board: 2 copper layers, 37.1 x 49.9 mm, 26 parts (4 on the bottom side), 31 nets.

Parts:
C12: 10uF; CP_Elec_5x5.4
C18, C19, C20: 0.1uF; C_0805_2012Metric
D13, D14, D15: LED; LED_0805_2012Metric
J1: Conn_01x06_Female; PinHeader_1x06_P2.54mm_Horizontal
J2, J4: Conn_01x16_Male; PinHeader_1x16_P2.54mm_Vertical
J3: CONUFL001-SMD-T; LINX_CONUFL001-SMD-T
J5: Conn_02x03_Odd_Even; PinHeader_2x03_P2.54mm_Vertical
J12: MEM2075-00-140-01-A; GCT_MEM2075-00-140-01-A
R2, R7, R37, R39, R41: 10K; R_0805_2012Metric
R15, R19: 100K; R_0805_2012Metric
R38: 330; R_0805_2012Metric
R40: 1K; R_0805_2012Metric
S3: FSM8JH; SW_FSM8JH
U1: ATmega328-AU; TQFP-32_7x7mm_P0.8mm
U4: COM-13909; MOD_COM-13909
Y1: 9C-8.000MEEJ-T; XTAL_9C-8.000MEEJ-T

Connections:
+3V3: C12.1, C19.1, J1.3, J2.1, J4.7, J5.2, J12.P4, R2.1, R7.1, R15.2, R19.2, R37.2, R39.1, R41.1, U1.4, U1.6, U1.18, U4.13
/AREF: C18.1, U1.20
/Card_Detect: J12.P9, R41.2, U1.14
/DTR: C20.1, J1.6
/G0: U1.2, U4.14
/G1: U1.9, U4.15
/G2: U1.11, U4.16
/Lora_CS: R15.1, U1.10, U4.5
/MISO: J4.9, J5.1, J12.P7, U1.16, U4.2
/MOSI: J4.10, J5.4, J12.P3, U1.15, U4.3
/PB0: J4.12, U1.12
/PB1: J4.11, U1.13
/PC0: J4.2, U1.23
/PC1: J4.1, U1.24
/PC3: J2.4, U1.26
/PD2: J2.8, U1.32
/PD3: J2.9, U1.1
/Reset: C20.2, J2.7, J5.5, R19.1, R39.2, S3.3, S3.4, U1.29, U4.6
/Rx: J1.5, U1.30
/SCK: J4.8, J5.3, J12.P5, R38.2, R40.2, U1.17, U4.4
/SCL: J2.6, R2.2, U1.28
/SDA: J2.5, R7.2, U1.27
/SD_CS: D15.1, J12.P2, U1.25
/Tx: J1.4, J2.3, U1.31
GND: C12.2, C18.2, C19.2, D13.1, D14.1, J1.1, J1.2, J2.2, J3.2, J3.3, J4.4, J5.6, J12.P6, J12.SH1, J12.SH2, J12.SH3, J12.SH4, S3.1, S3.2, U1.3, U1.5, U1.21, U4.1, U4.8, U4.10
unnamed: D13.2, R37.1
unnamed: D14.2, R38.1
unnamed: D15.2, R40.1
unnamed: J3.1, U4.9
unnamed: U1.7, Y1.1
unnamed: U1.8, Y1.2

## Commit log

2021-04-30 inital commit
2021-04-30 add readme
2021-05-27 update firmware
2021-06-15 added v0.2
2021-06-16 finalising version 0.2
2021-06-18 finalised v0.2
2021-06-21 added atmega lora module
2021-06-24 working arduino pro mini LoRaWAN
2021-06-25 minor update
2021-07-01 atmega328 needs RX <-> TX swap, button leads chopped, but LoRaWAN and SD Card working
2021-07-06 trying to optimise for atmega328
2021-07-07 atmega scale and lora, teensy sleep mode with lora clean wake up
2021-07-07 added v0.3
2021-07-08 updated v0.3 and sent for production
2021-07-16 updated v0.3 with interactive BOM
2021-07-19 teensy and atmega328 talking bytes
2021-07-20 working interrupt teensy atmega328
2021-07-20 update atmega328
2021-07-23 i2c, coms, memory working for teesny
2021-07-23 scale read and send working atmega328
2021-07-26 added interrupt disabling during measurment
2021-07-29 modified 9v resistor divider
2021-07-29 added config for weighscale and debug modes
2021-08-02 updated teensy side
2021-08-04 updated sleep config (19 mA with 4 mc's
2021-08-05 updated teensy for depolyment
2021-08-05 updated atmega for deployment
2021-08-05 updated file structure
2021-08-06 first deployment
2021-08-06 added calibration sketch
2021-08-16 updated for v0.4 and added additional schematic parts
2021-08-23 started on firmware for v0.4
2021-08-25 update v0.3 with weigh scale trigger fix
2021-08-29 update v0.3 atmega side
2021-08-30 update v0.3 with sd card functions
2021-09-01 second deployment of v0.3
2021-09-09 rm and update
2021-09-09 need to fix drink time for v0.4
2021-09-10 working on v0.4, temperature needs work
2021-09-15 deploy v0.4
2021-09-17 fixed power monitoring in v0.4
2021-09-20 added sleep mode during night-time
2021-09-21 Trivial changes to trigger a pull request & code review.
2021-09-21 Code review comments in-line. github pull request review only allows comments to be put on modified lines.
2021-11-14 added version 0.4.2 and 0.5
2021-11-25 added ibom for v0.5
2021-12-13 fixed stdev calc
2021-12-14 potenital fix for random device stoppage
2021-12-16 aligning master branch
2021-12-17 added watchdog timer
2021-12-19 added overtime (too long on scales) fix (hopefully)
2021-12-20 updated some functions that could fail?
2021-12-20 refactored scale scan function
2021-12-21 added payload position checking and changed error in check_state()
2021-12-22 added estimated weight function (need to change decoder)
2021-12-22 added decoder for the things network
2021-12-22 updated folder structure
2021-12-22 added lost main directory
2022-01-11 added citation.cff file
2022-01-13 cleaned and added docs
2022-01-14 Initial gh-pages commit
2022-01-14 Deploying to gh-pages from @ DPIclimate/ag-node@520e66dcd92712117caf8c7b60887d1e015661da 🚀
2022-01-14 updated readme and docs name
2022-01-14 updated doxygen style
2022-01-14 fixing main.yml
2022-01-14 Deploying to gh-pages from @ DPIclimate/ag-node@8aed944d7524e0c3fb97536e128ea6a38cbded89 🚀
2022-01-14 fixed stylesheet
2022-01-14 Deploying to gh-pages from @ DPIclimate/ag-node@50f902eb879b7692a4912adb540a170293845041 🚀
2022-01-14 fixed incorrect path
2022-01-14 added directory for css
2022-01-14 needed to add --strip-components=1
2022-01-14 Deploying to gh-pages from @ DPIclimate/ag-node@8471aab5ca9092b37d7bc6e635fcd0d07ddeeb8e 🚀
2022-01-17 updated decoder and added new parameters
2022-01-17 Deploying to gh-pages from @ DPIclimate/ag-node@70ffdf2fa25f442c2daadc67c5ec29809191ef7b 🚀
2022-01-24 updated with calibration data
2022-01-24 Deploying to gh-pages from @ DPIclimate/ag-node@e83eaaa660950511ce5e5f6bc13287e789b77f16 🚀
2022-01-27 added new analysis protocol and updated decoder
2022-01-27 Deploying to gh-pages from @ DPIclimate/ag-node@a82816c6bbc7b3a0564035d5008cf0f1fc02f773 🚀
2022-02-03 Create LICENSE
2022-02-14 added arduino shield
2022-02-14 added submodule
2022-02-14 Deploying to gh-pages from @ DPIclimate/ag-node@fac5a06857edf3fa3ddc33ad7b633ce8ea5409d0 🚀
2022-04-11 realign with master
2022-04-11 Deploying to gh-pages from @ DPIclimate/ag-node@0dc37cb46456940ff66b42026bdfa4aa38f3504c 🚀
2022-04-12 prepared final figures (schematic and pcb) for sup material
2022-09-01 updated figures and readme
2023-01-09 updated documentation and removed unnessessary htm files
2023-01-09 Deploying to gh-pages from @ DPIclimate/ag-node@9da5e6981fa5b4a6d39c24f8141f7dbc30c519e2 🚀
2023-01-09 removed arduino shield project and re-added .lib files for kicad components
2024-02-08 Switched to pio, fixed some typos and mssing braces.
